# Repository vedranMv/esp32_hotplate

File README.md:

ESP32 Reflow Hotplate
=====================

This repository contains electronics and an accompanying firmware for ESP32-powered hotplate from reflow soldering. The full project description can be found on [hackaday](https://hackaday.io/project/202351-reflow-soldering-hotplate).

Electronics schematics can be found in `electronics/` folder, together with a kicad project file and an accompanying PCB layout.

The remainder of folders belong to a pltaformio project for compiling the firmware. 

Features overview
-----------------

The list below contains the list of features supported by this project. Checked features are already implemented, the rest is pending development:

- [x] Heat element ON/OF
- [x] Plate temperature feedback
- [x] Internal temperature feedback
- [x] Input voltage feedback
- [x] Current power consumption
- [x] "Manual mode" - heat up and maintain given temperature
- [x] Configuration storage in non-volatile memory
- [ ] Timer indicating the time spent while heating up, reset when setpoint is reached to indicate the time spent at a setpoint
- [ ] "Profile mode" - follow a reflow profile for pre-programmed solder pastes
- [ ] Option to program a reflow profile via HMI
- Safety features:
  - [ ] Error if expecting to be heating up, but no temperature change is detected
  - [ ] Error if heating up for more 15 min
  - [ ] Error if temperature is 0

Software Design
---------------

To interact with the device, there's a user interface (HMI) consisting of OLED display and a rotary encoder with push button. Using push button gestures (click, double click and long press) it's possible to perform actions like edit/confirm/start/stop/etc, while rotary encoder can be used to scroll and increment data.

To make the best use of HMI, software is designed with the concept of 'applications'. Each application implements a device mode, or a behavior. For example, a manual mode is implemented as an app that allows the user to set manually a setpoint to which the hotplate heats up. User can select an active application, there can only be one active application at the time and the active application gets exclusive access to display and input. To see device stats (e.g. voltage, power, temperatures...), it's possible to change to stats app that shows all of that.

Apps interact with low level hardware via board support, that gives it access to analog and digital inputs/outputs or a configuration interface to load and save parameters from/to non-volatile storage.

Getting Started
---------------

This being a platformio project, getting started is realtively simple. If you have platformio already installed, it's enough to just clone this repository locally and open it in platformio. From there on, it's possible to build and upload the project to the target chip.

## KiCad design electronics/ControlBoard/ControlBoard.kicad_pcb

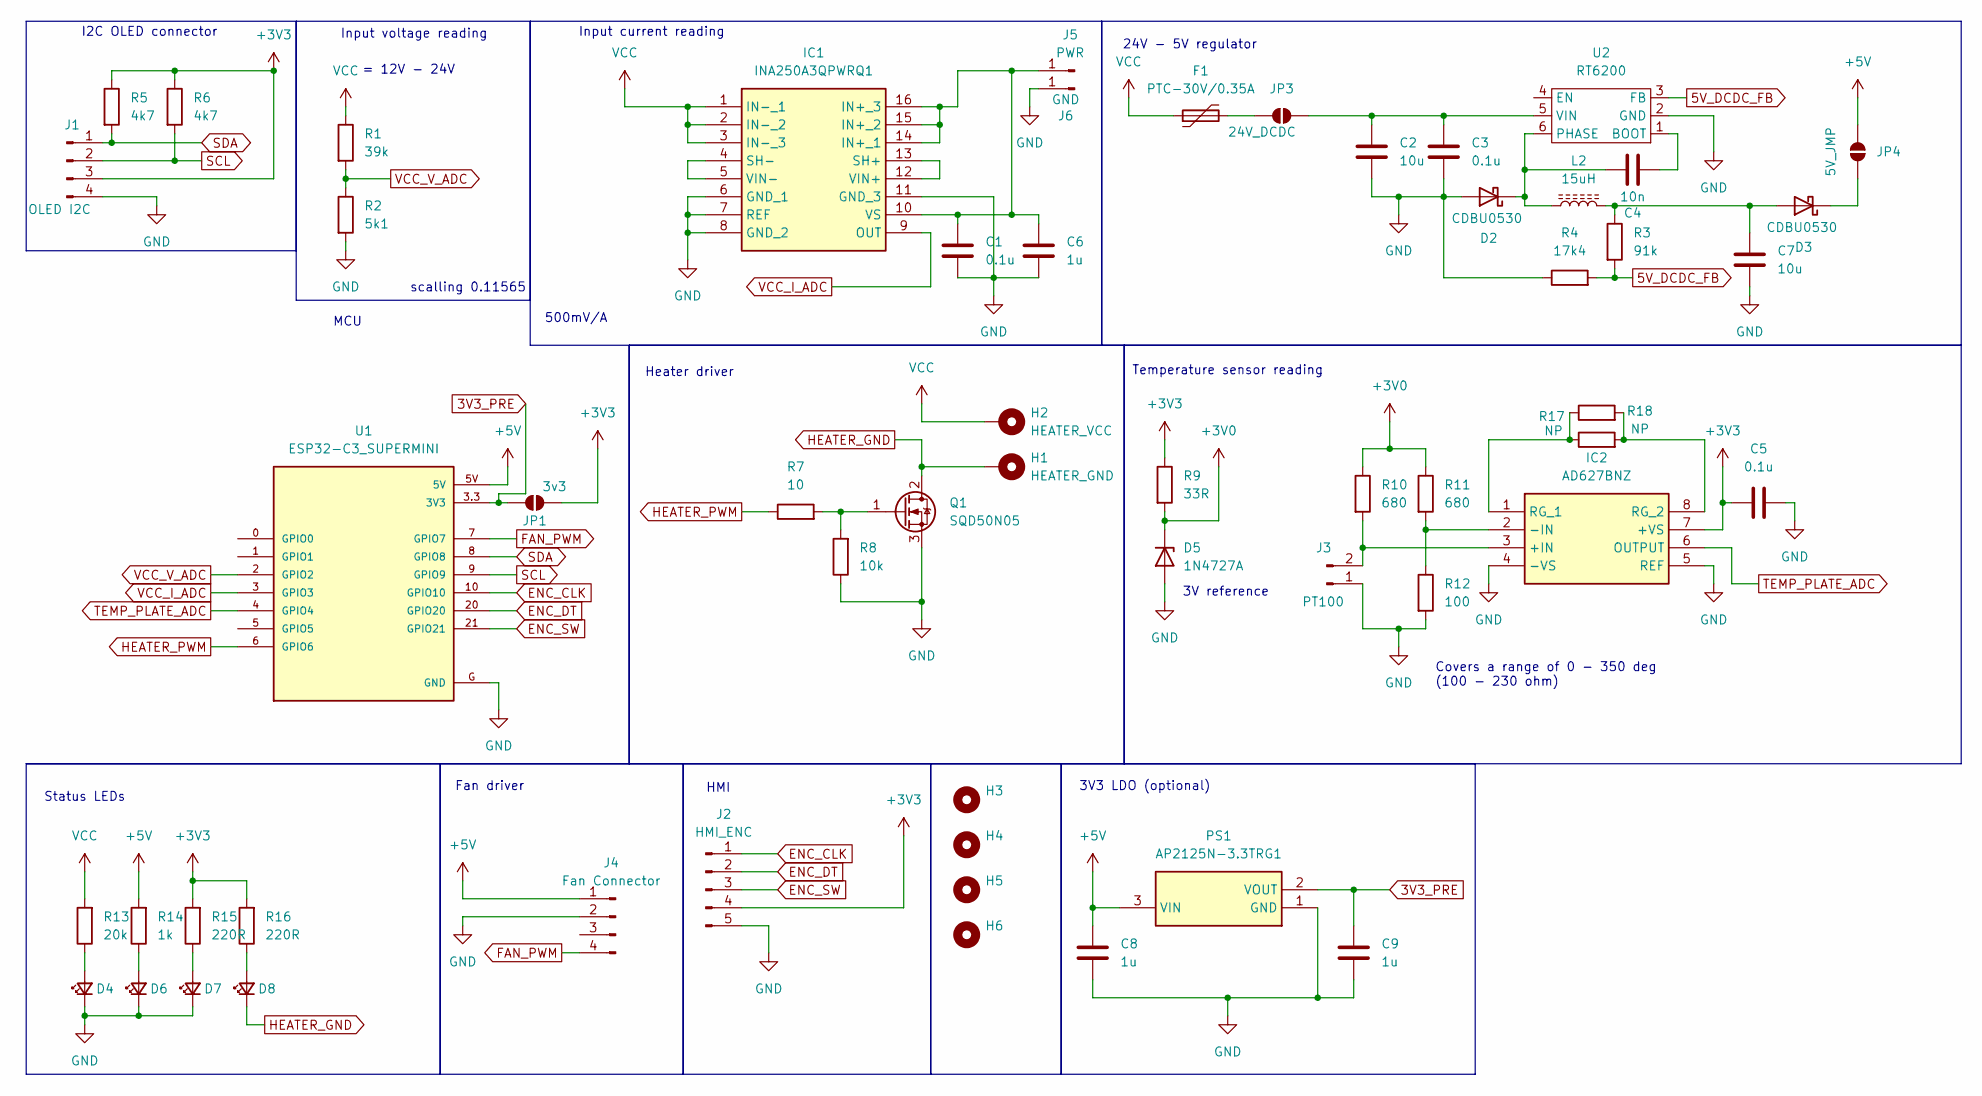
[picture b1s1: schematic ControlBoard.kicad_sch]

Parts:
C1, C5: 0.1u; R_0603_1608Metric_Pad0.98x0.95mm_HandSolder
C2: 10u; C_1210_3225Metric
C3: 0.1u; C_0603_1608Metric_Pad1.08x0.95mm_HandSolder
C4: 10n; C_0603_1608Metric_Pad1.08x0.95mm_HandSolder
C6, C8, C9: 1u; R_0603_1608Metric_Pad0.98x0.95mm_HandSolder
C7: 10u; C_0805_2012Metric_Pad1.18x1.45mm_HandSolder
D2, D3: CDBU0530; D_0603_1608Metric_Pad1.05x0.95mm_HandSolder
D4, D6, D7, D8: LED_0805_2012Metric_Pad1.15x1.40mm_HandSolder
D5: 1N4727A; D_DO-41_SOD81_P10.16mm_Horizontal
F1: PTC-30V/0.35A; Fuse_1206_3216Metric
H1: HEATER_GND; MountingHole_3.2mm_M3_DIN965_Pad
H2: HEATER_VCC; MountingHole_3.2mm_M3_DIN965_Pad
H3, H4, H5, H6: MountingHole; MountingHole_3.2mm_M3_ISO7380
IC1: INA250A3QPWRQ1; SOP65P640X120-16N; Manufacturer_Part_Number INA250A3QPWRQ1
IC2: AD627BNZ; DIP794W56P254L959H533Q8N; Manufacturer_Part_Number AD627BNZ
J1: OLED I2C; PinHeader_1x04_P2.54mm_Vertical
J2: HMI_ENC; PinHeader_1x05_P2.54mm_Vertical
J3: PT100; PinHeader_1x02_P2.54mm_Vertical
J4: Fan Connector; PinHeader_1x04_P2.54mm_Vertical
J5: PWR; TestPoint_Pad_4.0x4.0mm
J6: GND; TestPoint_Pad_4.0x4.0mm
JP1: 3v3; SolderJumper-2_P1.3mm_Open_RoundedPad1.0x1.5mm
JP3: 24V_DCDC; SolderJumper-2_P1.3mm_Open_RoundedPad1.0x1.5mm
JP4: 5V_JMP; SolderJumper-2_P1.3mm_Open_RoundedPad1.0x1.5mm
L2: 15uH; SRR4828A151M
PS1: AP2125N-3.3TRG1; SOT95P282X145-3N; Manufacturer_Part_Number AP2125N-3.3TRG1
Q1: SQD50N05; TO-252-2
R1: 39k; R_0805_2012Metric
R2: 5k1; R_0805_2012Metric
R3: 91k; R_0603_1608Metric_Pad0.98x0.95mm_HandSolder
R4: 17k4; R_0603_1608Metric_Pad0.98x0.95mm_HandSolder
R5, R6: 4k7; R_0805_2012Metric
R7: 10; R_0805_2012Metric
R8: 10k; R_0805_2012Metric
R9: 33R; R_0805_2012Metric
R10, R11: 680; R_0805_2012Metric
R12: 100; R_0805_2012Metric
R13: 20k; R_0603_1608Metric_Pad0.98x0.95mm_HandSolder
R14: 1k; R_0603_1608Metric_Pad0.98x0.95mm_HandSolder
R15, R16: 220R; R_0603_1608Metric_Pad0.98x0.95mm_HandSolder
R17, R18: NP; R_0805_2012Metric
U1: ESP32-C3_SUPERMINI; MODULE_ESP32-C3_SUPERMINI
U2: RT6200; SOT-23-6_Handsoldering

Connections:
3V3_PRE: C9.1, JP1.2 (B), PS1.2 (VOUT), U1.3.3 (3V3)
5V_DCDC_FB: R3.2, R4.2, U2.3 (FB)
+3V0: D5.1 (K), R9.2, R10.1, R11.1
+3V3: C5.2, IC2.7 (+VS), J1.3, J2.4, JP1.1 (A), R5.1, R6.1, R9.1, R15.2, R16.2
+5V: C8.1, J4.1, JP4.2 (B), PS1.3 (VIN), R14.2, U1.5V
ENC_CLK: J2.1, U1.10 (GPIO10)
ENC_DT: J2.2, U1.20 (GPIO20)
ENC_SW: J2.3, U1.21 (GPIO21)
FAN_PWM: J4.4, U1.7 (GPIO7)
GND: C1.1, C2.1, C3.1, C5.1, C6.1, C7.1, C8.2, C9.2, D2.2 (A), D4.1 (K), D5.2 (A), D6.1 (K), D7.1 (K), IC1.6 (GND_1), IC1.7 (REF), IC1.8 (GND_2), IC1.11 (GND_3), IC2.4 (-VS), IC2.5 (REF), J1.4, J2.5, J3.1, J4.2, J6.1, PS1.1 (GND), Q1.3 (S), R2.2, R4.1, R8.1, R12.2, U1.G (GND), U2.2 (GND)
HEATER_GND: D8.1 (K), H1.1, Q1.2 (D)
HEATER_PWM: R7.1, U1.6 (GPIO6)
unnamed: C4.1, D2.1 (K), L2.1, U2.6 (PHASE)
unnamed: C7.2, D3.2 (A), L2.2, R3.1
unnamed: D3.1 (K), JP4.1 (A)
unnamed: D4.2 (A), R13.1
unnamed: D6.2 (A), R14.1
unnamed: D7.2 (A), R15.1
unnamed: D8.2 (A), R16.1
unnamed: C1.2, C6.2, IC1.10 (VS), IC1.14 (IN+_1), IC1.15 (IN+_2), IC1.16 (IN+_3), J5.1
unnamed: IC1.12 (VIN+), IC1.13 (SH+)
unnamed: IC1.4 (SH-), IC1.5 (VIN-)
unnamed: IC2.3 (+IN), J3.2, R10.2
unnamed: IC2.2 (-IN), R11.2, R12.1
unnamed: IC2.1 (RG_1), R17.1, R18.1
unnamed: IC2.8 (RG_2), R17.2, R18.2
unnamed: F1.2, JP3.1 (A)
unnamed: C2.2, C3.2, JP3.2 (B), U2.5 (VIN)
unnamed: Q1.1 (G), R7.2, R8.2
unnamed: C4.2, U2.1 (BOOT)
SCL: J1.2, R6.2, U1.9 (GPIO9)
SDA: J1.1, R5.2, U1.8 (GPIO8)
TEMP_PLATE_ADC: IC2.6 (OUTPUT), U1.4 (GPIO4)
VCC: F1.1, H2.1, IC1.1 (IN-_1), IC1.2 (IN-_2), IC1.3 (IN-_3), R1.1, R13.2
VCC_I_ADC: IC1.9 (OUT), U1.3 (GPIO3)
VCC_V_ADC: R1.2, R2.1, U1.2 (GPIO2)

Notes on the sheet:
I2C OLED connector
Fan driver
Input current reading
Temperature sensor reading
HMI
= 12V - 24V
Input voltage reading
Status LEDs
3V reference
3V3 LDO (optional)
500mV/A
Heater driver
scalling 0.11565
MCU
Covers a range of 0 - 350 deg (100 - 230 ohm)
24V - 5V regulator

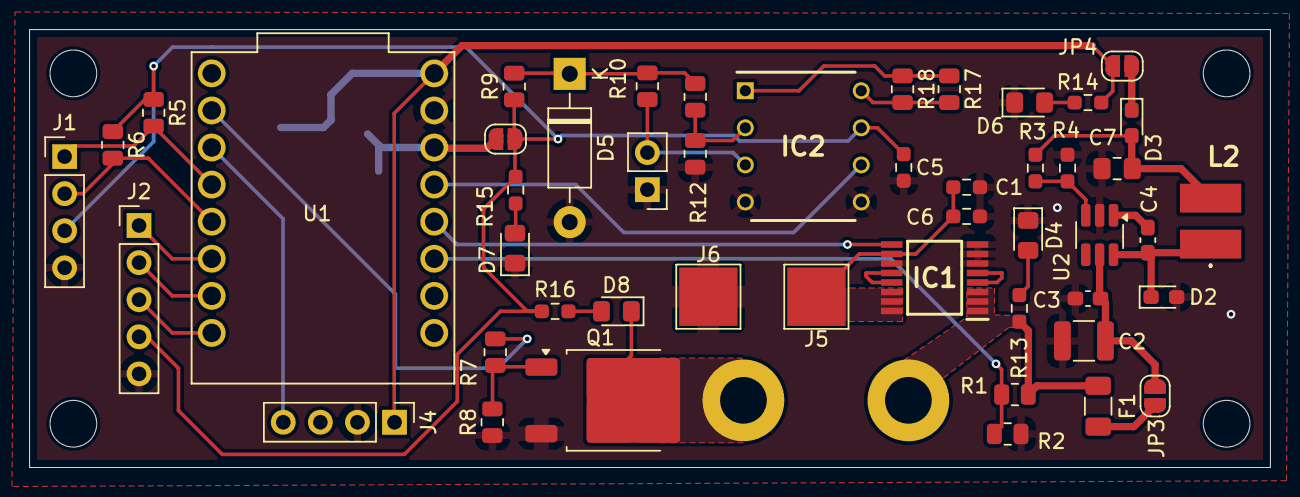
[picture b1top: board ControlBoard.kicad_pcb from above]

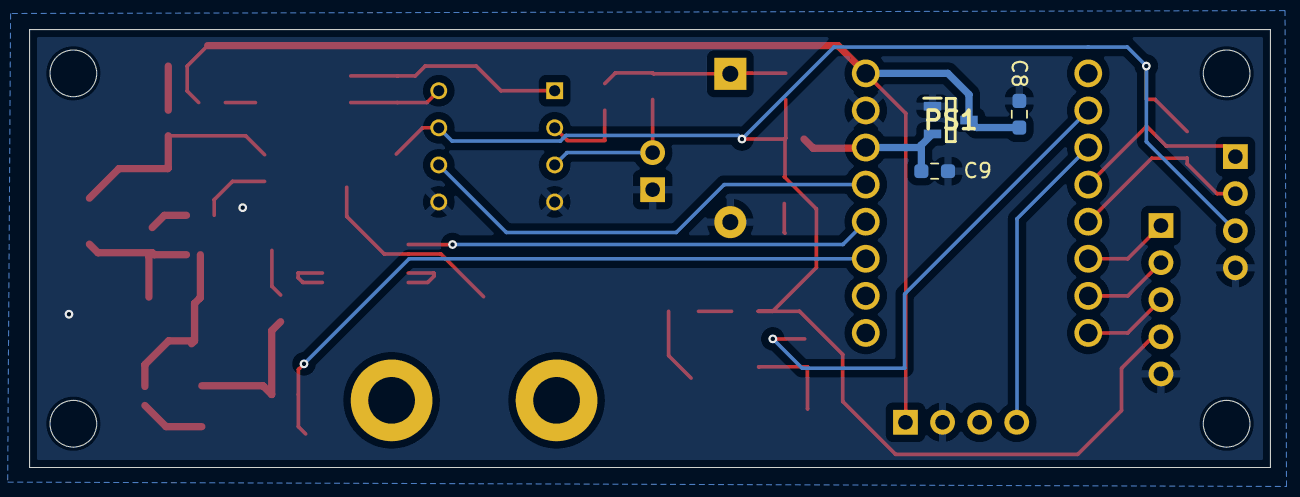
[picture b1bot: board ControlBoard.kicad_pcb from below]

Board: 2 copper layers, 85.0 x 30.0 mm, 57 parts (3 on the bottom side), 36 nets.

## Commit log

2025-02-08 Replace screen with app
2025-02-08 Remove pin definitions from a header
2025-02-08 Add NVS configuration
2025-02-08 Be more explicit about what's handled in ISR
2025-02-08 Add readme
